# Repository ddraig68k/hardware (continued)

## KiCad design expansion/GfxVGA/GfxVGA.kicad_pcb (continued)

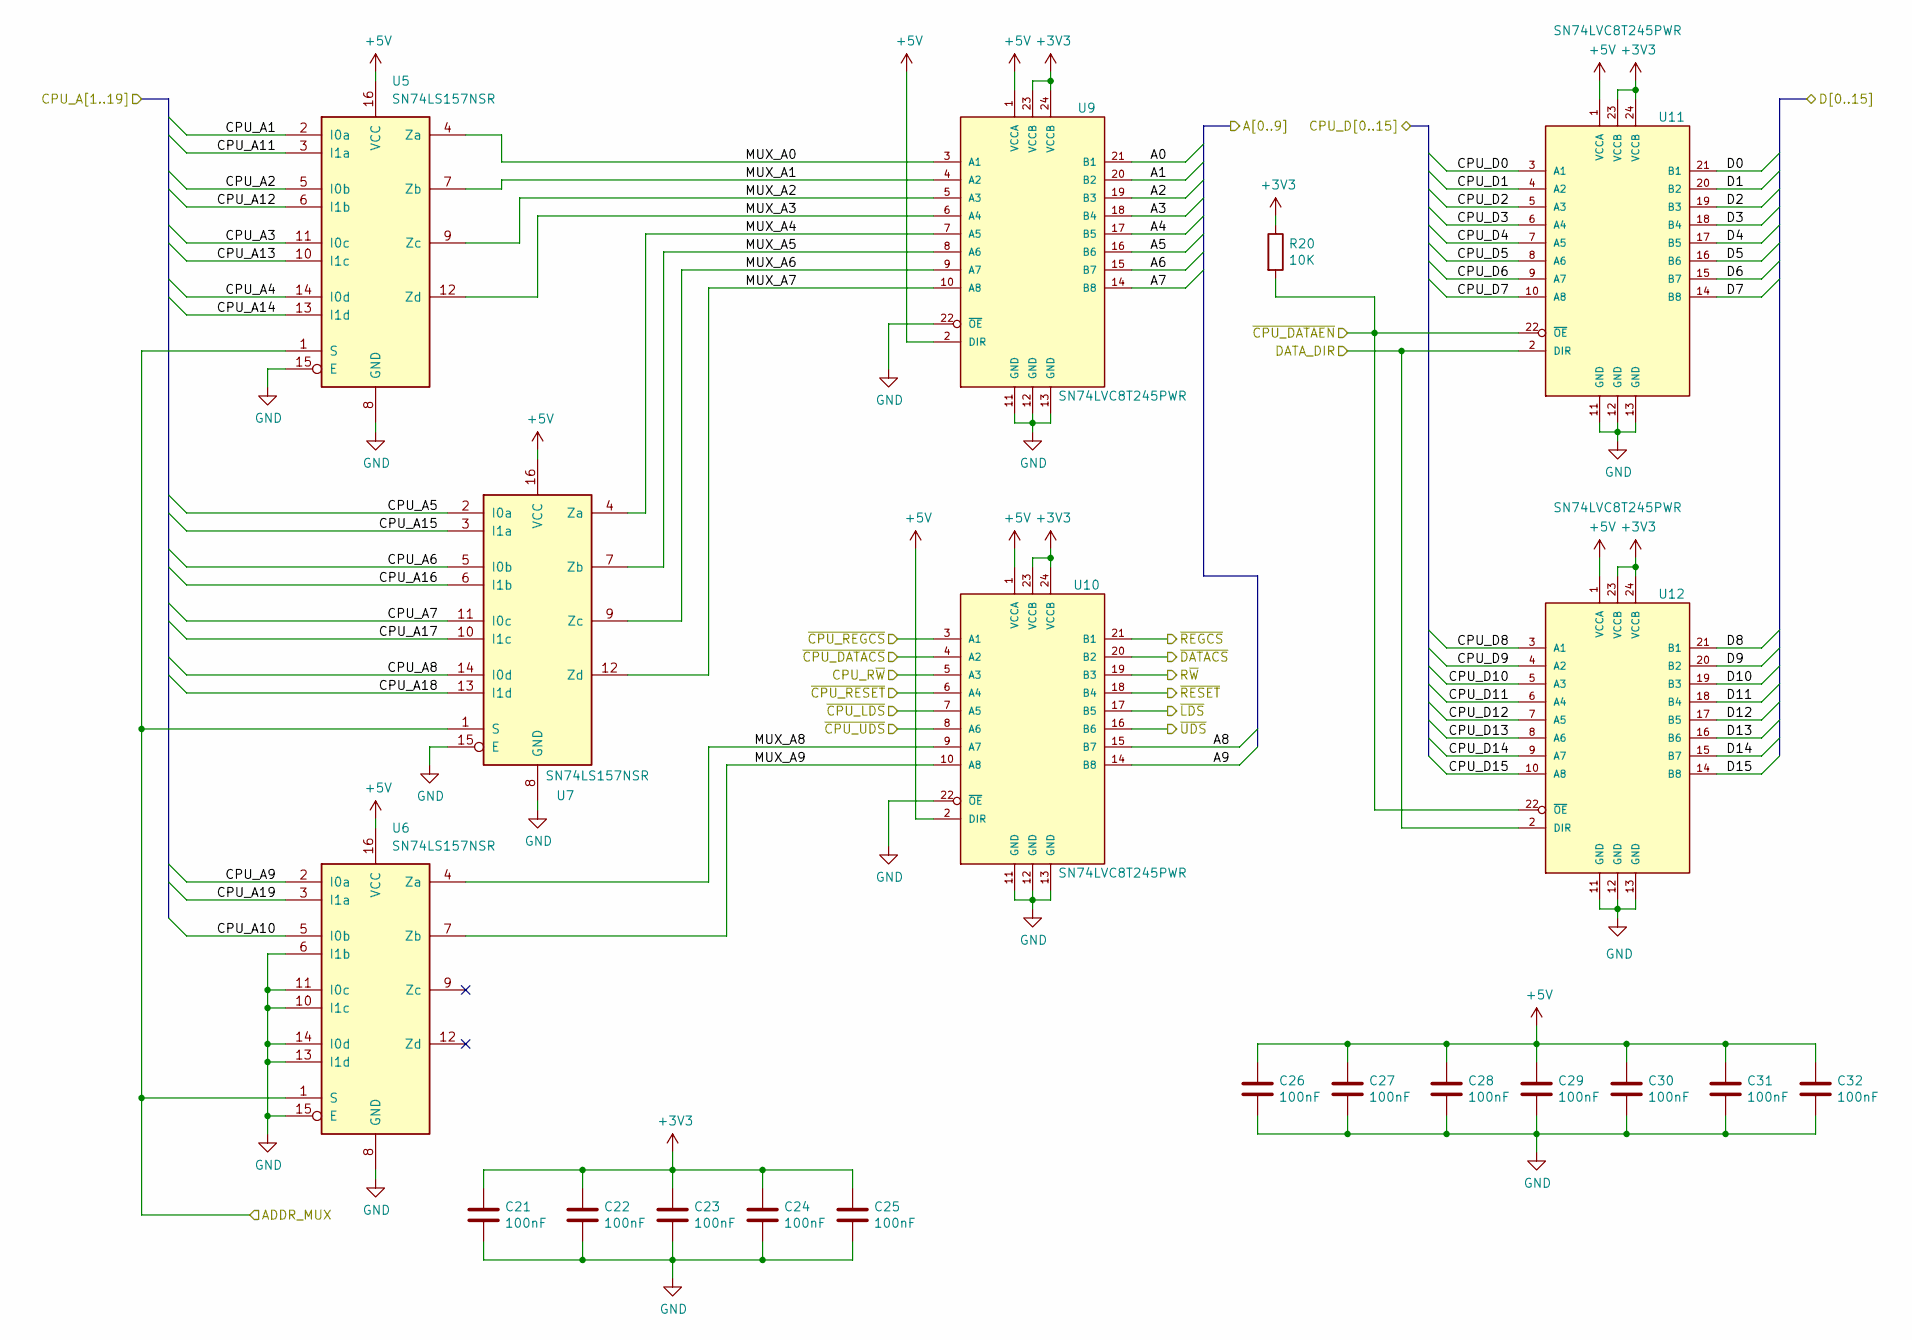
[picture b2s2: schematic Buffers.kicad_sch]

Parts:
C21, C22, C23, C24, C25, C26, C27, C28, C29, C30, C31, C32: 100nF; C_0805_2012Metric
R20: 10K; R_0805_2012Metric
U5, U6, U7: SN74LS157NSR; SO-16_5.3x10.2mm_P1.27mm
U9, U10, U11, U12: SN74LVC8T245PWR; SOP65P640X120-24N

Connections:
+3V3: C21.1, C22.1, C23.1, C24.1, C25.1, R20.1, U9.23 (VCCB), U9.24 (VCCB), U10.23 (VCCB), U10.24 (VCCB), U11.23 (VCCB), U11.24 (VCCB), U12.23 (VCCB), U12.24 (VCCB); also elsewhere on the board
+5V: C26.1, C27.1, C28.1, C29.1, C30.1, C31.1, C32.1, U5.16 (VCC), U6.16 (VCC), U7.16 (VCC), U9.1 (VCCA), U9.2 (DIR), U10.1 (VCCA), U10.2 (DIR), U11.1 (VCCA), U12.1 (VCCA); also elsewhere on the board
/CPU_A1: U5.2 (I0a); also elsewhere on the board
/CPU_A2: U5.5 (I0b); also elsewhere on the board
/CPU_A3: U5.11 (I0c); also elsewhere on the board
/CPU_A4: U5.14 (I0d); also elsewhere on the board
/CPU_A5: U7.2 (I0a); also elsewhere on the board
/CPU_A6: U7.5 (I0b); also elsewhere on the board
/CPU_A7: U7.11 (I0c); also elsewhere on the board
/CPU_A8: U7.14 (I0d); also elsewhere on the board
/CPU_A9: U6.2 (I0a); also elsewhere on the board
/CPU_A10: U6.5 (I0b); also elsewhere on the board
/CPU_A11: U5.3 (I1a); also elsewhere on the board
/CPU_A12: U5.6 (I1b); also elsewhere on the board
/CPU_A13: U5.10 (I1c); also elsewhere on the board
/CPU_A14: U5.13 (I1d); also elsewhere on the board
/CPU_A15: U7.3 (I1a); also elsewhere on the board
/CPU_A16: U7.6 (I1b); also elsewhere on the board
/CPU_A17: U7.10 (I1c); also elsewhere on the board
/CPU_A18: U7.13 (I1d); also elsewhere on the board
/CPU_A19: U6.3 (I1a); also elsewhere on the board
/CPU_D0: U11.3 (A1); also elsewhere on the board
/CPU_D1: U11.4 (A2); also elsewhere on the board
/CPU_D2: U11.5 (A3); also elsewhere on the board
/CPU_D3: U11.6 (A4); also elsewhere on the board
/CPU_D4: U11.7 (A5); also elsewhere on the board
/CPU_D5: U11.8 (A6); also elsewhere on the board
/CPU_D6: U11.9 (A7); also elsewhere on the board
/CPU_D7: U11.10 (A8); also elsewhere on the board
/CPU_D8: U12.3 (A1); also elsewhere on the board
/CPU_D9: U12.4 (A2); also elsewhere on the board
/CPU_D10: U12.5 (A3); also elsewhere on the board
/CPU_D11: U12.6 (A4); also elsewhere on the board
/CPU_D12: U12.7 (A5); also elsewhere on the board
/CPU_D13: U12.8 (A6); also elsewhere on the board
/CPU_D14: U12.9 (A7); also elsewhere on the board
/CPU_D15: U12.10 (A8); also elsewhere on the board
/CPU_R~W: U10.5 (A3); also elsewhere on the board
/FPGA/A0: U9.21 (B1); also elsewhere on the board
/FPGA/A1: U9.20 (B2); also elsewhere on the board
/FPGA/A2: U9.19 (B3); also elsewhere on the board
/FPGA/A3: U9.18 (B4); also elsewhere on the board
/FPGA/A4: U9.17 (B5); also elsewhere on the board
/FPGA/A5: U9.16 (B6); also elsewhere on the board
/FPGA/A6: U9.15 (B7); also elsewhere on the board
/FPGA/A7: U9.14 (B8); also elsewhere on the board
/FPGA/A8: U10.15 (B7); also elsewhere on the board
/FPGA/A9: U10.14 (B8); also elsewhere on the board
/FPGA/ADDR_MUX: U5.1 (S), U6.1 (S), U7.1 (S); also elsewhere on the board
/FPGA/D0: U11.21 (B1); also elsewhere on the board
/FPGA/D1: U11.20 (B2); also elsewhere on the board
/FPGA/D2: U11.19 (B3); also elsewhere on the board
/FPGA/D3: U11.18 (B4); also elsewhere on the board
/FPGA/D4: U11.17 (B5); also elsewhere on the board
/FPGA/D5: U11.16 (B6); also elsewhere on the board
/FPGA/D6: U11.15 (B7); also elsewhere on the board
/FPGA/D7: U11.14 (B8); also elsewhere on the board
/FPGA/D8: U12.21 (B1); also elsewhere on the board
/FPGA/D9: U12.20 (B2); also elsewhere on the board
/FPGA/D10: U12.19 (B3); also elsewhere on the board
/FPGA/D11: U12.18 (B4); also elsewhere on the board
/FPGA/D12: U12.17 (B5); also elsewhere on the board
/FPGA/D13: U12.16 (B6); also elsewhere on the board
/FPGA/D14: U12.15 (B7); also elsewhere on the board
/FPGA/D15: U12.14 (B8); also elsewhere on the board
/FPGA/DATA_DIR: U11.2 (DIR), U12.2 (DIR); also elsewhere on the board
/FPGA/R~W: U10.19 (B3); also elsewhere on the board
/FPGA/~CPU_DATAEN: R20.2, U11.22 (~OE), U12.22 (~OE); also elsewhere on the board
/FPGA/~DATACS: U10.20 (B2); also elsewhere on the board
/FPGA/~LDS: U10.17 (B5); also elsewhere on the board
/FPGA/~REGCS: U10.21 (B1); also elsewhere on the board
/FPGA/~RESET: U10.18 (B4); also elsewhere on the board
/FPGA/~UDS: U10.16 (B6); also elsewhere on the board
/Level Translators/MUX_A0: U5.4 (Za), U9.3 (A1)
/Level Translators/MUX_A1: U5.7 (Zb), U9.4 (A2)
/Level Translators/MUX_A2: U5.9 (Zc), U9.5 (A3)
/Level Translators/MUX_A3: U5.12 (Zd), U9.6 (A4)
/Level Translators/MUX_A4: U7.4 (Za), U9.7 (A5)
/Level Translators/MUX_A5: U7.7 (Zb), U9.8 (A6)
/Level Translators/MUX_A6: U7.9 (Zc), U9.9 (A7)
/Level Translators/MUX_A7: U7.12 (Zd), U9.10 (A8)
/Level Translators/MUX_A8: U6.4 (Za), U10.9 (A7)
/Level Translators/MUX_A9: U6.7 (Zb), U10.10 (A8)
/~CPU_DATACS: U10.4 (A2); also elsewhere on the board
/~CPU_LDS: U10.7 (A5); also elsewhere on the board
/~CPU_REGCS: U10.3 (A1); also elsewhere on the board
/~CPU_RESET: U10.6 (A4); also elsewhere on the board
/~CPU_UDS: U10.8 (A6); also elsewhere on the board
GND: C21.2, C22.2, C23.2, C24.2, C25.2, C26.2, C27.2, C28.2, C29.2, C30.2, C31.2, C32.2, U5.8 (GND), U5.15 (E), U6.6 (I1b), U6.8 (GND), U6.10 (I1c), U6.11 (I0c), U6.13 (I1d), U6.14 (I0d), U6.15 (E), U7.8 (GND), U7.15 (E), U9.11 (GND), U9.12 (GND), U9.13 (GND), U9.22 (~OE), U10.11 (GND), U10.12 (GND), U10.13 (GND), U10.22 (~OE), U11.11 (GND), U11.12 (GND), U11.13 (GND), U12.11 (GND), U12.12 (GND), U12.13 (GND); also elsewhere on the board

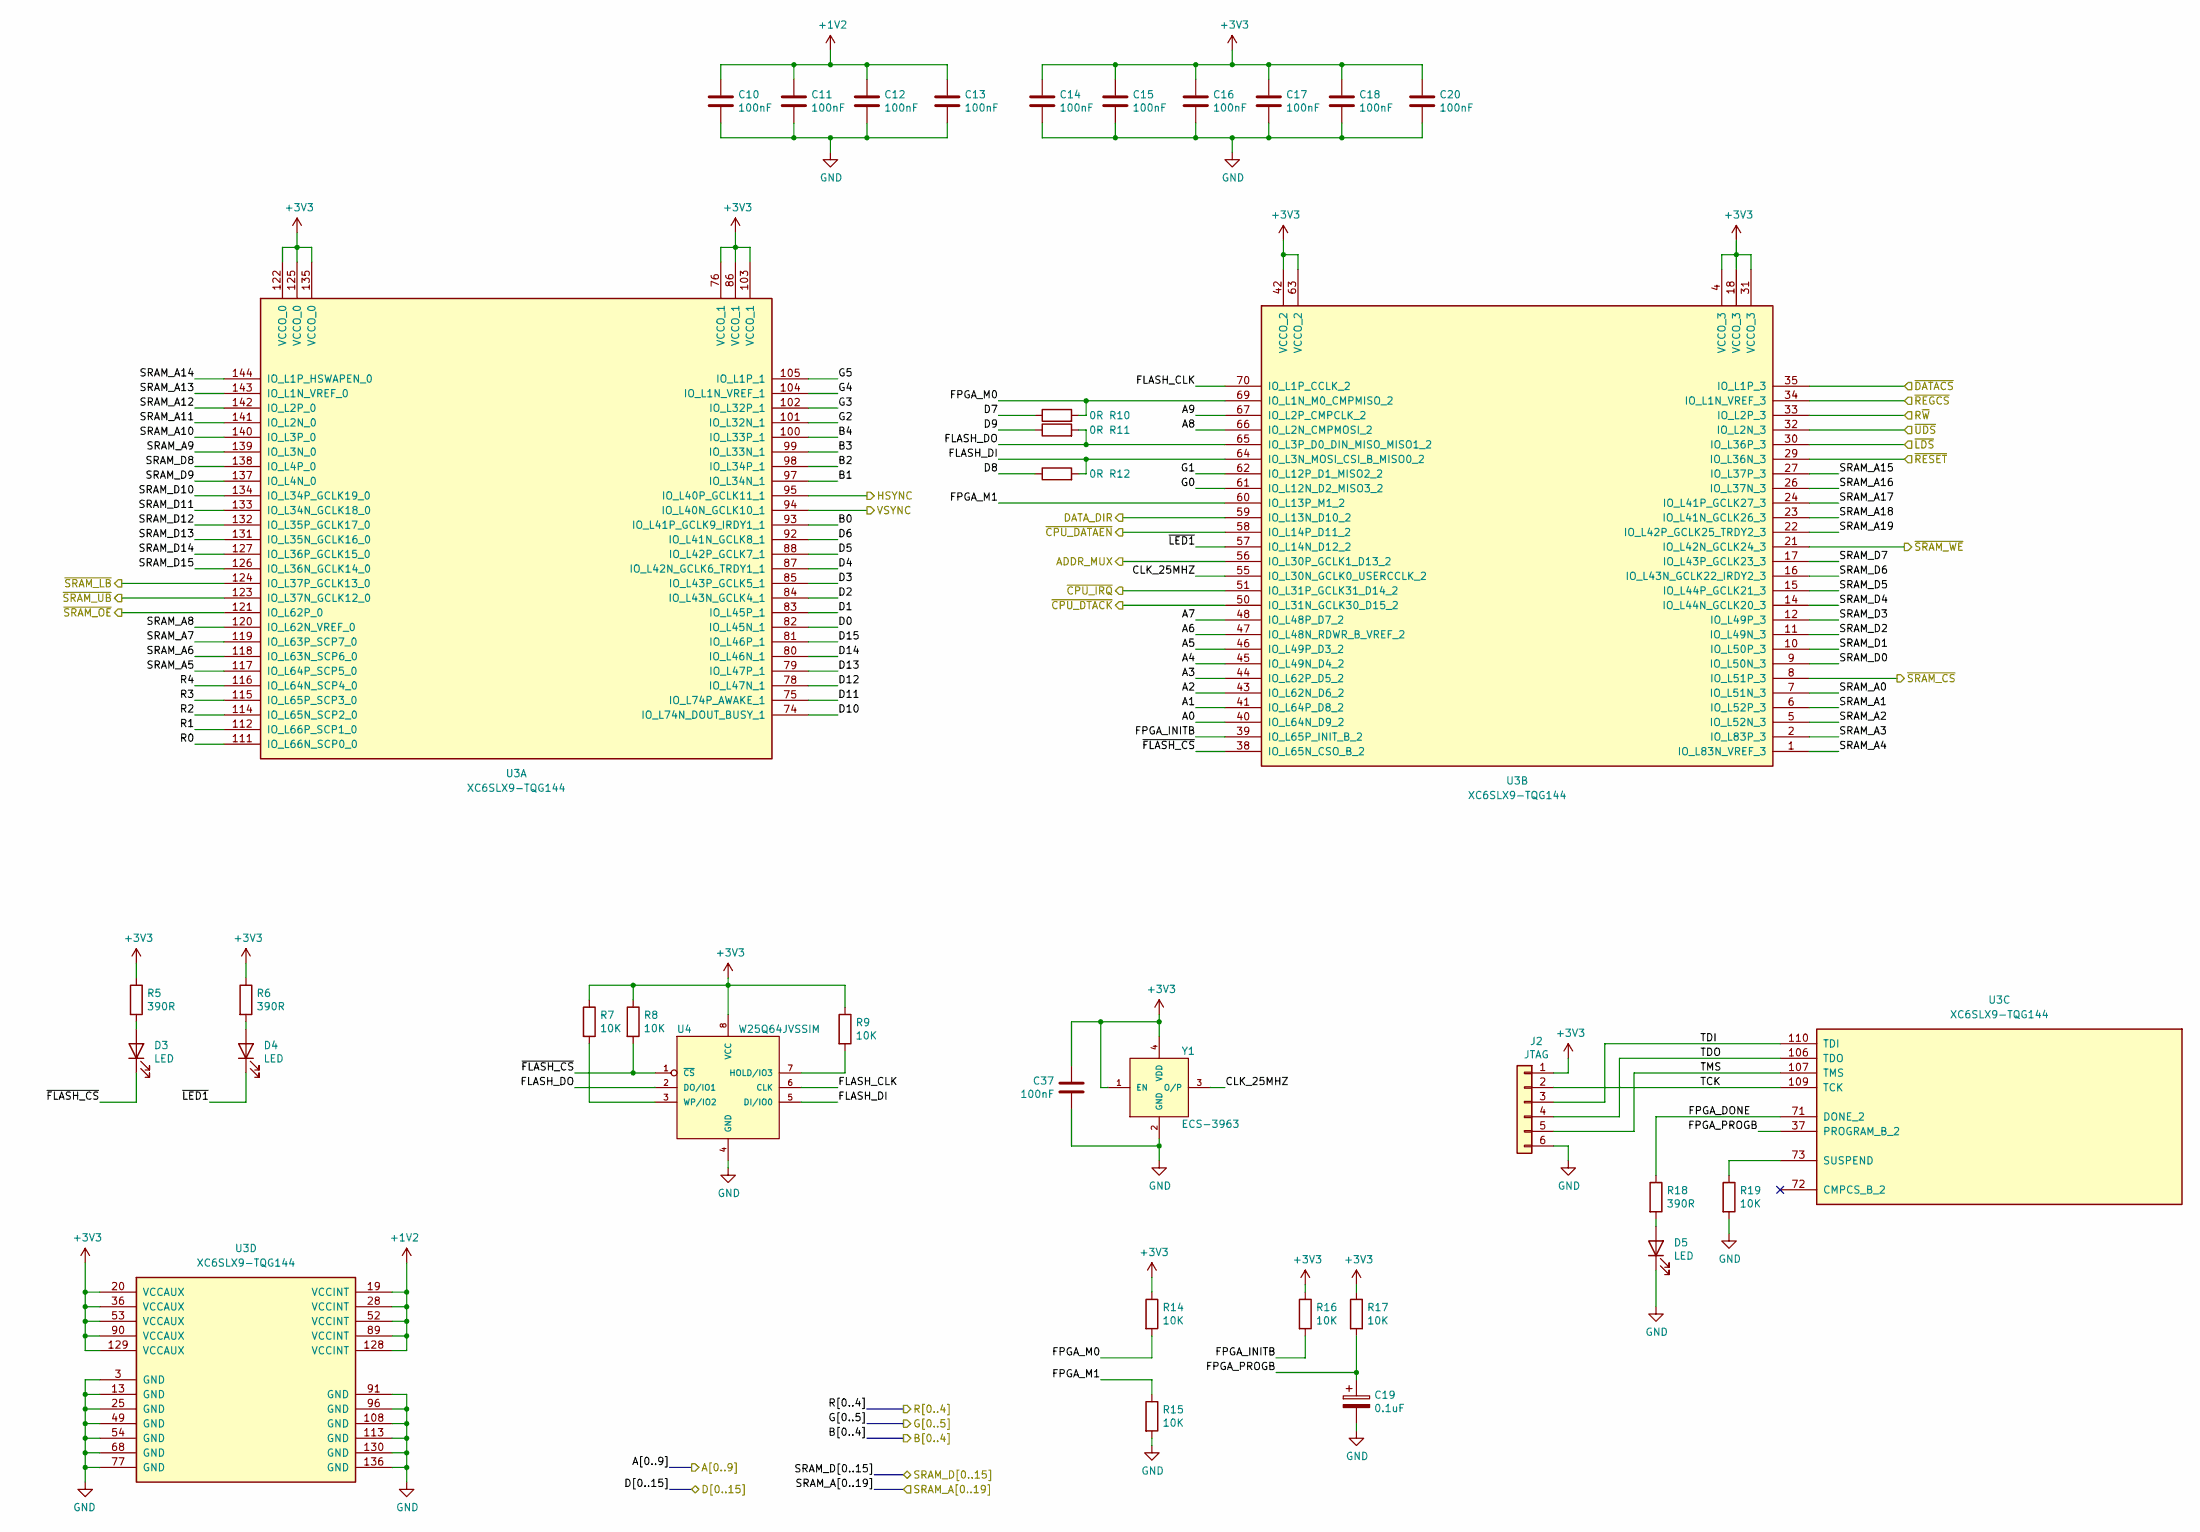
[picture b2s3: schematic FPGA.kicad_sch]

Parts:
C10, C11, C12, C13, C14, C15, C16, C17, C18, C20, C37: 100nF; C_0805_2012Metric
C19: 0.1uF; CP_Elec_4x5.3
D3, D4, D5: LED; LED_1206_3216Metric
J2: JTAG; PinHeader_1x06_P2.54mm_Vertical
R5, R6, R18: 390R; R_0805_2012Metric
R7, R8, R9, R14, R15, R16, R17, R19: 10K; R_0805_2012Metric
R10, R11, R12: 0R; R_0805_2012Metric
U3: XC6SLX9-TQG144; TQ144
U4: W25Q64JVSSIM; SOIC127P790X195-8N
Y1: ECS-3963; OSC_ECS-3963; PARTREV N/A

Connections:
+1V2: C10.1, C11.1, C12.1, C13.1, U3.19 (VCCINT), U3.28 (VCCINT), U3.52 (VCCINT), U3.89 (VCCINT), U3.128 (VCCINT); also elsewhere on the board
+3V3: C14.1, C15.1, C16.1, C17.1, C18.1, C20.1, C37.1, J2.1, R5.1, R6.1, R7.1, R8.1, R9.1, R14.1, R16.1, R17.1, U3.4 (VCCO_3), U3.18 (VCCO_3), U3.20 (VCCAUX), U3.31 (VCCO_3), U3.36 (VCCAUX), U3.42 (VCCO_2), U3.53 (VCCAUX), U3.63 (VCCO_2), U3.76 (VCCO_1), U3.86 (VCCO_1), U3.90 (VCCAUX), U3.103 (VCCO_1), U3.122 (VCCO_0), U3.125 (VCCO_0), U3.129 (VCCAUX), U3.135 (VCCO_0), U4.8 (VCC), Y1.1 (EN), Y1.4 (VDD); also elsewhere on the board
/FPGA/A0: U3.40 (IO_L64N_D9_2); also elsewhere on the board
/FPGA/A1: U3.41 (IO_L64P_D8_2); also elsewhere on the board
/FPGA/A2: U3.43 (IO_L62N_D6_2); also elsewhere on the board
/FPGA/A3: U3.44 (IO_L62P_D5_2); also elsewhere on the board
/FPGA/A4: U3.45 (IO_L49N_D4_2); also elsewhere on the board
/FPGA/A5: U3.46 (IO_L49P_D3_2); also elsewhere on the board
/FPGA/A6: U3.47 (IO_L48N_RDWR_B_VREF_2); also elsewhere on the board
/FPGA/A7: U3.48 (IO_L48P_D7_2); also elsewhere on the board
/FPGA/A8: U3.66 (IO_L2N_CMPMOSI_2); also elsewhere on the board
/FPGA/A9: U3.67 (IO_L2P_CMPCLK_2); also elsewhere on the board
/FPGA/ADDR_MUX: U3.56 (IO_L30P_GCLK1_D13_2); also elsewhere on the board
/FPGA/B0: U3.93 (IO_L41P_GCLK9_IRDY1_1); also elsewhere on the board
/FPGA/B1: U3.97 (IO_L34N_1); also elsewhere on the board
/FPGA/B2: U3.98 (IO_L34P_1); also elsewhere on the board
/FPGA/B3: U3.99 (IO_L33N_1); also elsewhere on the board
/FPGA/B4: U3.100 (IO_L33P_1); also elsewhere on the board
/FPGA/CLK_25MHZ: U3.55 (IO_L30N_GCLK0_USERCCLK_2), Y1.3 (O/P)
/FPGA/D0: U3.82 (IO_L45N_1); also elsewhere on the board
/FPGA/D1: U3.83 (IO_L45P_1); also elsewhere on the board
/FPGA/D2: U3.84 (IO_L43N_GCLK4_1); also elsewhere on the board
/FPGA/D3: U3.85 (IO_L43P_GCLK5_1); also elsewhere on the board
/FPGA/D4: U3.87 (IO_L42N_GCLK6_TRDY1_1); also elsewhere on the board
/FPGA/D5: U3.88 (IO_L42P_GCLK7_1); also elsewhere on the board
/FPGA/D6: U3.92 (IO_L41N_GCLK8_1); also elsewhere on the board
/FPGA/D7: R10.1; also elsewhere on the board
/FPGA/D8: R12.1; also elsewhere on the board
/FPGA/D9: R11.1; also elsewhere on the board
/FPGA/D10: U3.74 (IO_L74N_DOUT_BUSY_1); also elsewhere on the board
/FPGA/D11: U3.75 (IO_L74P_AWAKE_1); also elsewhere on the board
/FPGA/D12: U3.78 (IO_L47N_1); also elsewhere on the board
/FPGA/D13: U3.79 (IO_L47P_1); also elsewhere on the board
/FPGA/D14: U3.80 (IO_L46N_1); also elsewhere on the board
/FPGA/D15: U3.81 (IO_L46P_1); also elsewhere on the board
/FPGA/DATA_DIR: U3.59 (IO_L13N_D10_2); also elsewhere on the board
/FPGA/FLASH_CLK: U3.70 (IO_L1P_CCLK_2), U4.6 (CLK)
/FPGA/FLASH_DI: R12.2, U3.64 (IO_L3N_MOSI_CSI_B_MISO0_2), U4.5 (DI/IO0)
/FPGA/FLASH_DO: R11.2, U3.65 (IO_L3P_D0_DIN_MISO_MISO1_2), U4.2 (DO/IO1)
/FPGA/FPGA_DONE: R18.1, U3.71 (DONE_2)
/FPGA/FPGA_INITB: R16.2, U3.39 (IO_L65P_INIT_B_2)
/FPGA/FPGA_M0: R10.2, R14.2, U3.69 (IO_L1N_M0_CMPMISO_2)
/FPGA/FPGA_M1: R15.1, U3.60 (IO_L13P_M1_2)
/FPGA/FPGA_PROGB: C19.1, R17.2, U3.37 (PROGRAM_B_2)
/FPGA/G0: U3.61 (IO_L12N_D2_MISO3_2); also elsewhere on the board
/FPGA/G1: U3.62 (IO_L12P_D1_MISO2_2); also elsewhere on the board
/FPGA/G2: U3.101 (IO_L32N_1); also elsewhere on the board
/FPGA/G3: U3.102 (IO_L32P_1); also elsewhere on the board
/FPGA/G4: U3.104 (IO_L1N_VREF_1); also elsewhere on the board
/FPGA/G5: U3.105 (IO_L1P_1); also elsewhere on the board
/FPGA/HSYNC: U3.95 (IO_L40P_GCLK11_1); also elsewhere on the board
/FPGA/R0: U3.111 (IO_L66N_SCP0_0); also elsewhere on the board
/FPGA/R1: U3.112 (IO_L66P_SCP1_0); also elsewhere on the board
/FPGA/R2: U3.114 (IO_L65N_SCP2_0); also elsewhere on the board
/FPGA/R3: U3.115 (IO_L65P_SCP3_0); also elsewhere on the board
/FPGA/R4: U3.116 (IO_L64N_SCP4_0); also elsewhere on the board
/FPGA/R~W: U3.33 (IO_L2P_3); also elsewhere on the board
/FPGA/SRAM_A0: U3.7 (IO_L51N_3); also elsewhere on the board
/FPGA/SRAM_A1: U3.6 (IO_L52P_3); also elsewhere on the board
/FPGA/SRAM_A2: U3.5 (IO_L52N_3); also elsewhere on the board
/FPGA/SRAM_A3: U3.2 (IO_L83P_3); also elsewhere on the board
/FPGA/SRAM_A4: U3.1 (IO_L83N_VREF_3); also elsewhere on the board
/FPGA/SRAM_A5: U3.117 (IO_L64P_SCP5_0); also elsewhere on the board
/FPGA/SRAM_A6: U3.118 (IO_L63N_SCP6_0); also elsewhere on the board
/FPGA/SRAM_A7: U3.119 (IO_L63P_SCP7_0); also elsewhere on the board
/FPGA/SRAM_A8: U3.120 (IO_L62N_VREF_0); also elsewhere on the board
/FPGA/SRAM_A9: U3.139 (IO_L3N_0); also elsewhere on the board
/FPGA/SRAM_A10: U3.140 (IO_L3P_0); also elsewhere on the board
/FPGA/SRAM_A11: U3.141 (IO_L2N_0); also elsewhere on the board
/FPGA/SRAM_A12: U3.142 (IO_L2P_0); also elsewhere on the board
/FPGA/SRAM_A13: U3.143 (IO_L1N_VREF_0); also elsewhere on the board
/FPGA/SRAM_A14: U3.144 (IO_L1P_HSWAPEN_0); also elsewhere on the board
/FPGA/SRAM_A15: U3.27 (IO_L37P_3); also elsewhere on the board
/FPGA/SRAM_A16: U3.26 (IO_L37N_3); also elsewhere on the board
/FPGA/SRAM_A17: U3.24 (IO_L41P_GCLK27_3); also elsewhere on the board
/FPGA/SRAM_A18: U3.23 (IO_L41N_GCLK26_3); also elsewhere on the board
/FPGA/SRAM_A19: U3.22 (IO_L42P_GCLK25_TRDY2_3); also elsewhere on the board
/FPGA/SRAM_D0: U3.9 (IO_L50N_3); also elsewhere on the board
/FPGA/SRAM_D1: U3.10 (IO_L50P_3); also elsewhere on the board
/FPGA/SRAM_D2: U3.11 (IO_L49N_3); also elsewhere on the board
/FPGA/SRAM_D3: U3.12 (IO_L49P_3); also elsewhere on the board
/FPGA/SRAM_D4: U3.14 (IO_L44N_GCLK20_3); also elsewhere on the board
/FPGA/SRAM_D5: U3.15 (IO_L44P_GCLK21_3); also elsewhere on the board
/FPGA/SRAM_D6: U3.16 (IO_L43N_GCLK22_IRDY2_3); also elsewhere on the board
/FPGA/SRAM_D7: U3.17 (IO_L43P_GCLK23_3); also elsewhere on the board
/FPGA/SRAM_D8: U3.138 (IO_L4P_0); also elsewhere on the board
/FPGA/SRAM_D9: U3.137 (IO_L4N_0); also elsewhere on the board
/FPGA/SRAM_D10: U3.134 (IO_L34P_GCLK19_0); also elsewhere on the board
/FPGA/SRAM_D11: U3.133 (IO_L34N_GCLK18_0); also elsewhere on the board
/FPGA/SRAM_D12: U3.132 (IO_L35P_GCLK17_0); also elsewhere on the board
/FPGA/SRAM_D13: U3.131 (IO_L35N_GCLK16_0); also elsewhere on the board
/FPGA/SRAM_D14: U3.127 (IO_L36P_GCLK15_0); also elsewhere on the board
/FPGA/SRAM_D15: U3.126 (IO_L36N_GCLK14_0); also elsewhere on the board
/FPGA/TCK: J2.2, U3.109 (TCK)
/FPGA/TDI: J2.3, U3.110 (TDI)
/FPGA/TDO: J2.4, U3.106 (TDO)
/FPGA/TMS: J2.5, U3.107 (TMS)
/FPGA/VSYNC: U3.94 (IO_L40N_GCLK10_1); also elsewhere on the board
/FPGA/~CPU_DATAEN: U3.58 (IO_L14P_D11_2); also elsewhere on the board
/FPGA/~DATACS: U3.35 (IO_L1P_3); also elsewhere on the board
/FPGA/~FLASH_CS: D3.1 (K), R8.2, U3.38 (IO_L65N_CSO_B_2), U4.1 (~CS)
/FPGA/~LDS: U3.30 (IO_L36P_3); also elsewhere on the board
/FPGA/~LED1: D4.1 (K), U3.57 (IO_L14N_D12_2)
/FPGA/~REGCS: U3.34 (IO_L1N_VREF_3); also elsewhere on the board
/FPGA/~RESET: U3.29 (IO_L36N_3); also elsewhere on the board
/FPGA/~SRAM_CS: U3.8 (IO_L51P_3); also elsewhere on the board
/FPGA/~SRAM_LB: U3.124 (IO_L37P_GCLK13_0); also elsewhere on the board
/FPGA/~SRAM_OE: U3.121 (IO_L62P_0); also elsewhere on the board
/FPGA/~SRAM_UB: U3.123 (IO_L37N_GCLK12_0); also elsewhere on the board
/FPGA/~SRAM_WE: U3.21 (IO_L42N_GCLK24_3); also elsewhere on the board
/FPGA/~UDS: U3.32 (IO_L2N_3); also elsewhere on the board
/~CPU_DTACK: U3.50 (IO_L31N_GCLK30_D15_2); also elsewhere on the board
/~CPU_IRQ: U3.51 (IO_L31P_GCLK31_D14_2); also elsewhere on the board
GND: C10.2, C11.2, C12.2, C13.2, C14.2, C15.2, C16.2, C17.2, C18.2, C19.2, C20.2, C37.2, D5.1 (K), J2.6, R15.2, R19.2, U3.3 (GND), U3.13 (GND), U3.25 (GND), U3.49 (GND), U3.54 (GND), U3.68 (GND), U3.77 (GND), U3.91 (GND), U3.96 (GND), U3.108 (GND), U3.113 (GND), U3.130 (GND), U3.136 (GND), U4.4 (GND), Y1.2 (GND); also elsewhere on the board
unnamed: D3.2 (A), R5.2
unnamed: D4.2 (A), R6.2
unnamed: D5.2 (A), R18.2
unnamed: R19.1, U3.73 (SUSPEND)
unnamed: R9.2, U4.7 (HOLD/IO3)
unnamed: R7.2, U4.3 (WP/IO2)

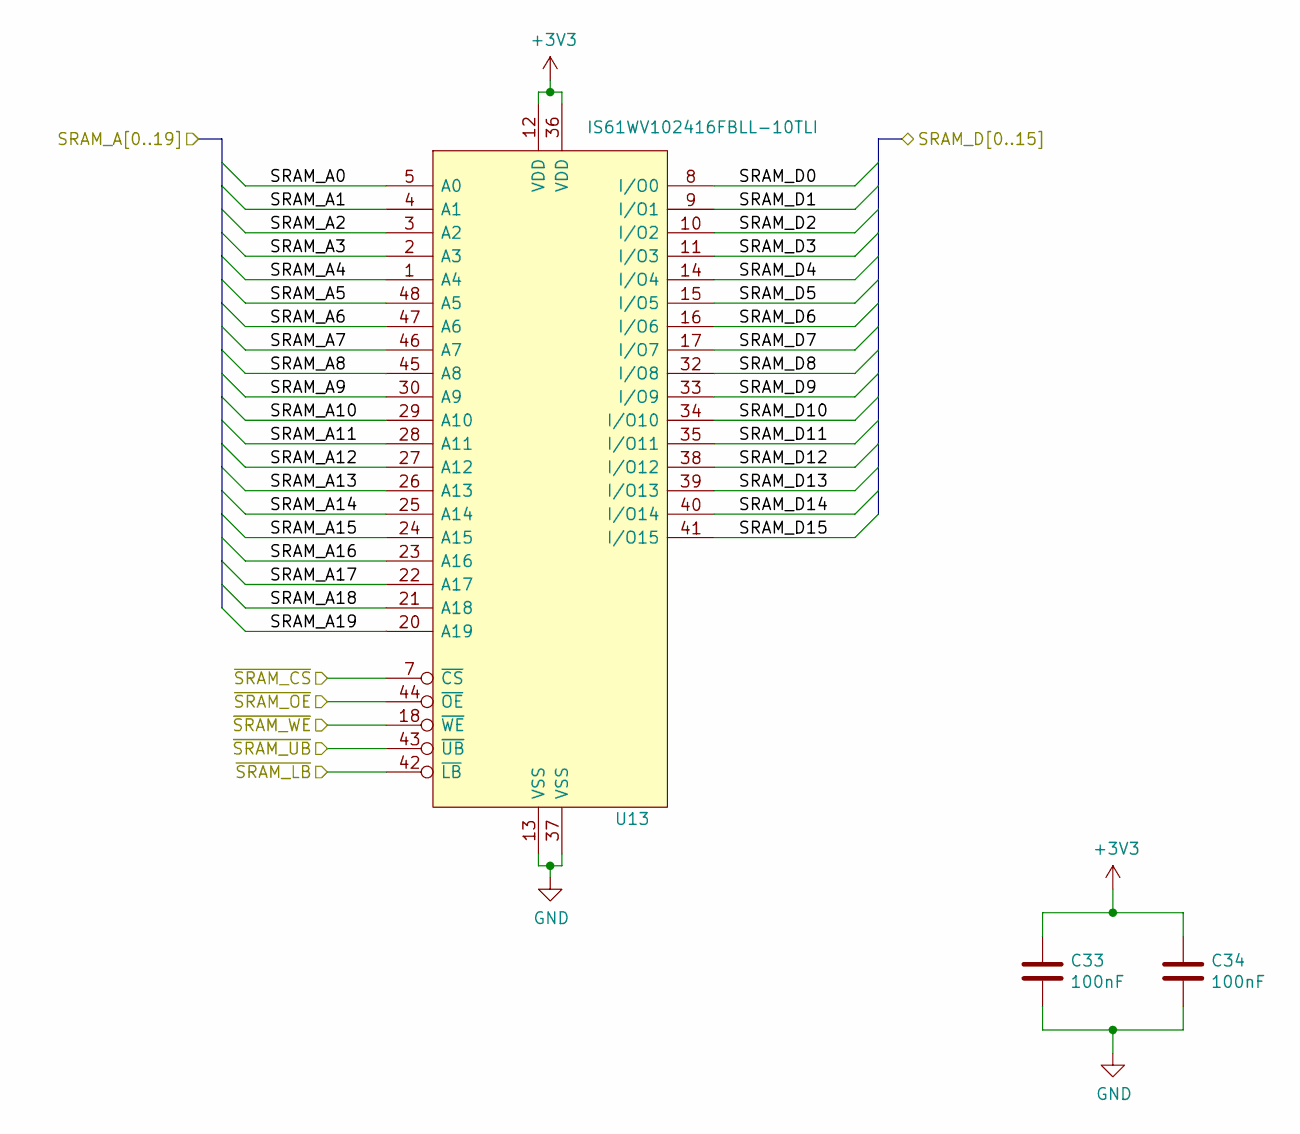
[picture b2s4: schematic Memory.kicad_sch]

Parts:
C33, C34: 100nF; C_0805_2012Metric
U13: IS61WV102416FBLL-10TLI; SOP50P2000X120-48N; Manufacturer_Part_Number IS61WV102416FBLL-10TLI; Mouser Part Number 870-61WV12416FBL1TLI

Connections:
+3V3: C33.1, C34.1, U13.12 (VDD), U13.36 (VDD); also elsewhere on the board
/FPGA/SRAM_A0: U13.5 (A0); also elsewhere on the board
/FPGA/SRAM_A1: U13.4 (A1); also elsewhere on the board
/FPGA/SRAM_A2: U13.3 (A2); also elsewhere on the board
/FPGA/SRAM_A3: U13.2 (A3); also elsewhere on the board
/FPGA/SRAM_A4: U13.1 (A4); also elsewhere on the board
/FPGA/SRAM_A5: U13.48 (A5); also elsewhere on the board
/FPGA/SRAM_A6: U13.47 (A6); also elsewhere on the board
/FPGA/SRAM_A7: U13.46 (A7); also elsewhere on the board
/FPGA/SRAM_A8: U13.45 (A8); also elsewhere on the board
/FPGA/SRAM_A9: U13.30 (A9); also elsewhere on the board
/FPGA/SRAM_A10: U13.29 (A10); also elsewhere on the board
/FPGA/SRAM_A11: U13.28 (A11); also elsewhere on the board
/FPGA/SRAM_A12: U13.27 (A12); also elsewhere on the board
/FPGA/SRAM_A13: U13.26 (A13); also elsewhere on the board
/FPGA/SRAM_A14: U13.25 (A14); also elsewhere on the board
/FPGA/SRAM_A15: U13.24 (A15); also elsewhere on the board
/FPGA/SRAM_A16: U13.23 (A16); also elsewhere on the board
/FPGA/SRAM_A17: U13.22 (A17); also elsewhere on the board
/FPGA/SRAM_A18: U13.21 (A18); also elsewhere on the board
/FPGA/SRAM_A19: U13.20 (A19); also elsewhere on the board
/FPGA/SRAM_D0: U13.8 (I/O0); also elsewhere on the board
/FPGA/SRAM_D1: U13.9 (I/O1); also elsewhere on the board
/FPGA/SRAM_D2: U13.10 (I/O2); also elsewhere on the board
/FPGA/SRAM_D3: U13.11 (I/O3); also elsewhere on the board
/FPGA/SRAM_D4: U13.14 (I/O4); also elsewhere on the board
/FPGA/SRAM_D5: U13.15 (I/O5); also elsewhere on the board
/FPGA/SRAM_D6: U13.16 (I/O6); also elsewhere on the board
/FPGA/SRAM_D7: U13.17 (I/O7); also elsewhere on the board
/FPGA/SRAM_D8: U13.32 (I/O8); also elsewhere on the board
/FPGA/SRAM_D9: U13.33 (I/O9); also elsewhere on the board
/FPGA/SRAM_D10: U13.34 (I/O10); also elsewhere on the board
/FPGA/SRAM_D11: U13.35 (I/O11); also elsewhere on the board
/FPGA/SRAM_D12: U13.38 (I/O12); also elsewhere on the board
/FPGA/SRAM_D13: U13.39 (I/O13); also elsewhere on the board
/FPGA/SRAM_D14: U13.40 (I/O14); also elsewhere on the board
/FPGA/SRAM_D15: U13.41 (I/O15); also elsewhere on the board
/FPGA/~SRAM_CS: U13.7 (~CS); also elsewhere on the board
/FPGA/~SRAM_LB: U13.42 (~LB); also elsewhere on the board
/FPGA/~SRAM_OE: U13.44 (~OE); also elsewhere on the board
/FPGA/~SRAM_UB: U13.43 (~UB); also elsewhere on the board
/FPGA/~SRAM_WE: U13.18 (~WE); also elsewhere on the board
GND: C33.2, C34.2, U13.13 (VSS), U13.37 (VSS); also elsewhere on the board

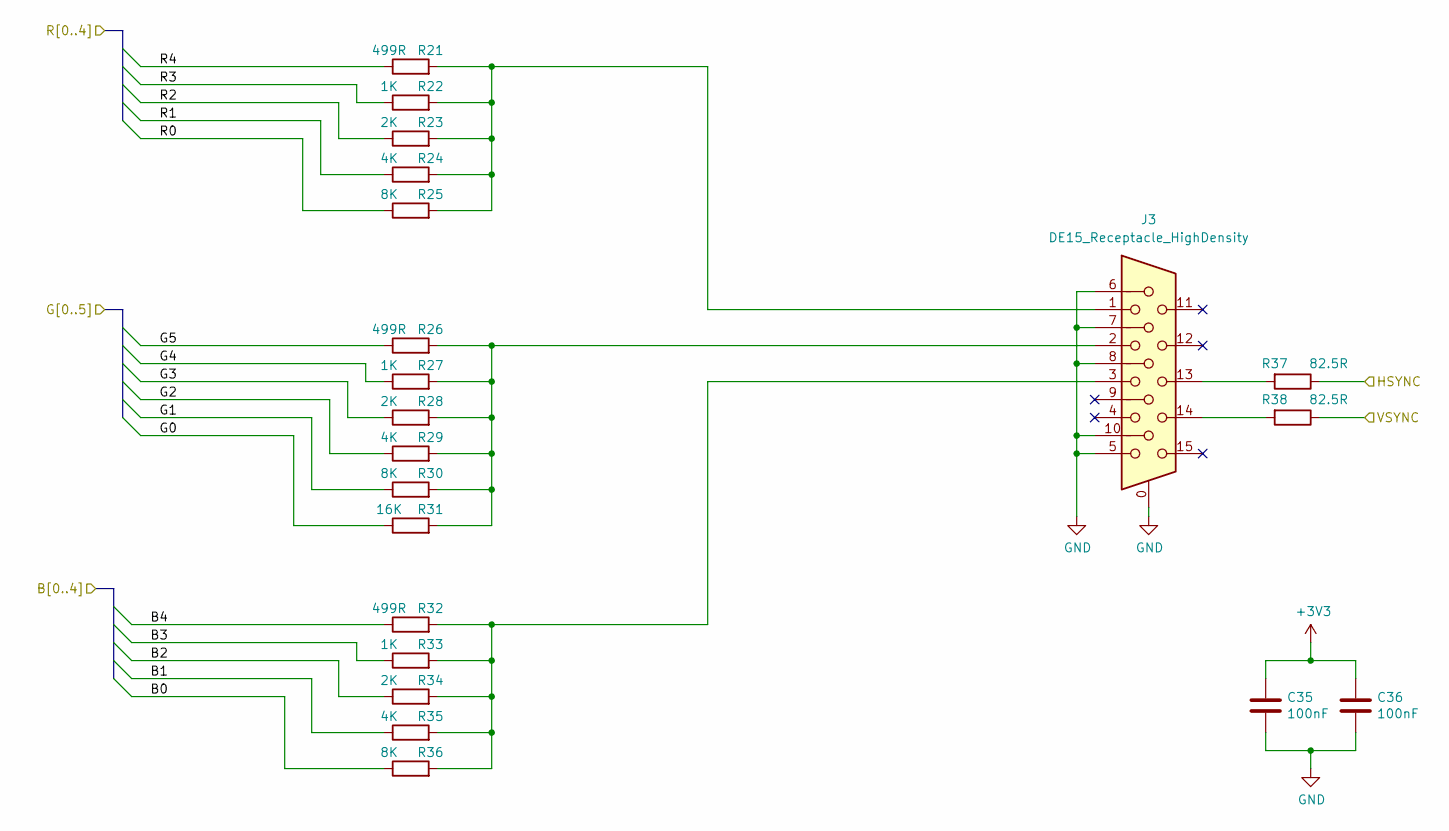
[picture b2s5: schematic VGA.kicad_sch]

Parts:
C35, C36: 100nF; C_0805_2012Metric
J3: DE15_Receptacle_HighDensity; DSUB-15-HD_Female_Horizontal_P2.29x1.98mm_EdgePinOffset3.03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
R21, R26, R32: 499R; R_0805_2012Metric
R22, R27, R33: 1K; R_0805_2012Metric
R23, R28, R34: 2K; R_0805_2012Metric
R24, R29, R35: 4K; R_0805_2012Metric
R25, R30, R36: 8K; R_0805_2012Metric
R31: 16K; R_0805_2012Metric
R37, R38: 82.5R; R_0805_2012Metric

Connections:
+3V3: C35.1, C36.1; also elsewhere on the board
/FPGA/B0: R36.1; also elsewhere on the board
/FPGA/B1: R35.1; also elsewhere on the board
/FPGA/B2: R34.1; also elsewhere on the board
/FPGA/B3: R33.1; also elsewhere on the board
/FPGA/B4: R32.1; also elsewhere on the board
/FPGA/G0: R31.1; also elsewhere on the board
/FPGA/G1: R30.1; also elsewhere on the board
/FPGA/G2: R29.1; also elsewhere on the board
/FPGA/G3: R28.1; also elsewhere on the board
/FPGA/G4: R27.1; also elsewhere on the board
/FPGA/G5: R26.1; also elsewhere on the board
/FPGA/HSYNC: R37.1; also elsewhere on the board
/FPGA/R0: R25.1; also elsewhere on the board
/FPGA/R1: R24.1; also elsewhere on the board
/FPGA/R2: R23.1; also elsewhere on the board
/FPGA/R3: R22.1; also elsewhere on the board
/FPGA/R4: R21.1; also elsewhere on the board
/FPGA/VSYNC: R38.1; also elsewhere on the board
GND: C35.2, C36.2, J3.0, J3.5, J3.6, J3.7, J3.8, J3.10; also elsewhere on the board
unnamed: J3.1, R21.2, R22.2, R23.2, R24.2, R25.2
unnamed: J3.2, R26.2, R27.2, R28.2, R29.2, R30.2, R31.2
unnamed: J3.3, R32.2, R33.2, R34.2, R35.2, R36.2
unnamed: J3.13, R37.2
unnamed: J3.14, R38.2
